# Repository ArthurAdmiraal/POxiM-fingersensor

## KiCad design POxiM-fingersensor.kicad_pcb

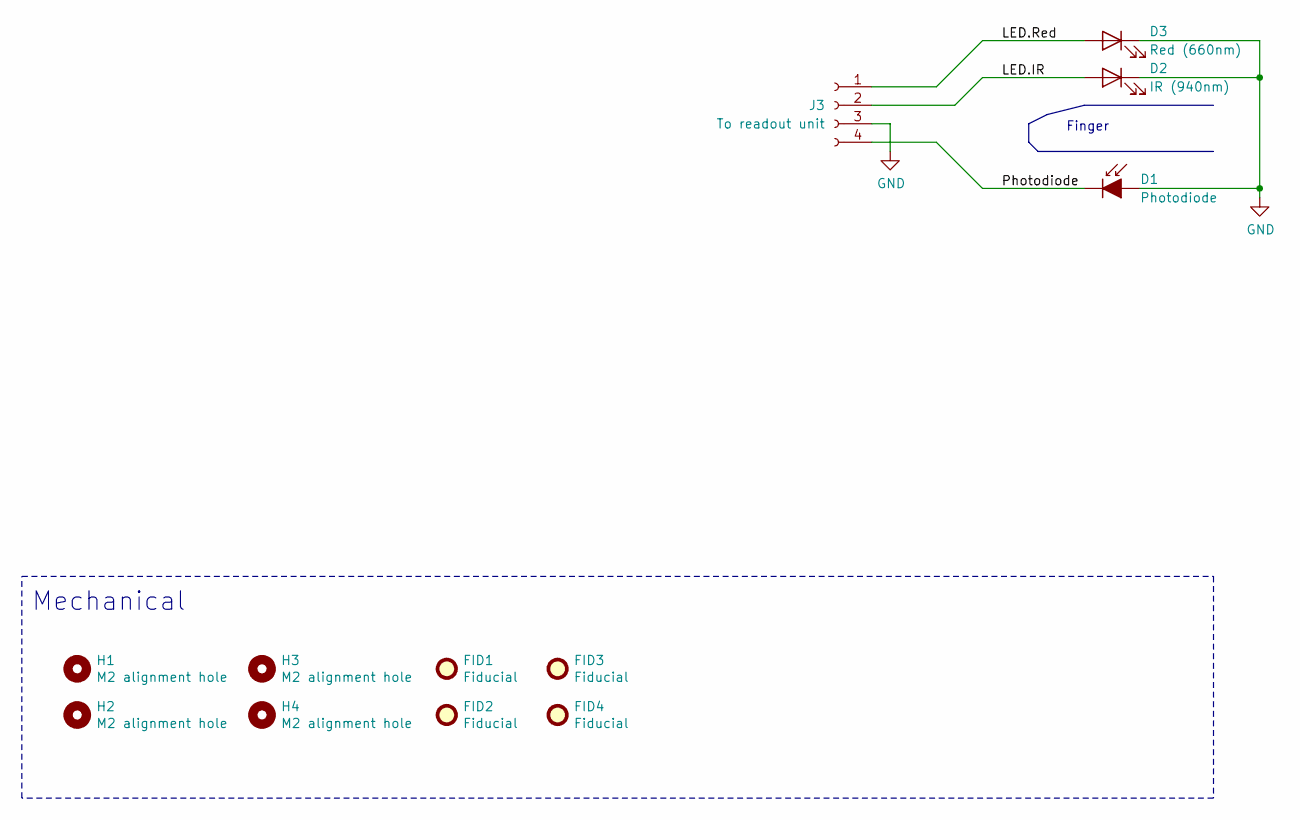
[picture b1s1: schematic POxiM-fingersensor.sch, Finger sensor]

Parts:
D1: Photodiode; LED_1206_3216Metric_0805_2012Metric_Castellated; Part number SFH 2701
D2: IR (940nm); LED_0805_2012Metric_0603_1608Metric; Part number APTD2012F3C
D3: Red (660nm); LED_0805_2012Metric_0603_1608Metric; Part number SML-LX0603SRW-TR
FID1, FID2, FID3, FID4: Fiducial; Fiducial_1mm_Mask2mm
H1, H2, H3, H4: M2 alignment hole; AlignmentHole_2mm
J3: To readout unit; Finger-CableConnection

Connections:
/LED.IR: D2.2 (A), J3.2
/LED.Red: D3.2 (A), J3.1
/Photodiode: D1.1 (K), J3.4
GND: D1.2 (A), D2.1 (K), D3.1 (K), J3.3

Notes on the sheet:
Finger
Mechanical

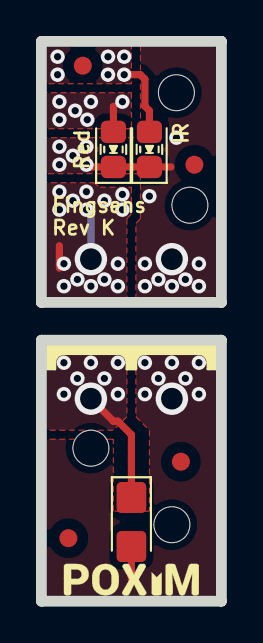
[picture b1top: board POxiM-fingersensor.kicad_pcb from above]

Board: 2 copper layers, 10.0 x 31.1 mm, 12 parts (1 on the bottom side), 4 nets.

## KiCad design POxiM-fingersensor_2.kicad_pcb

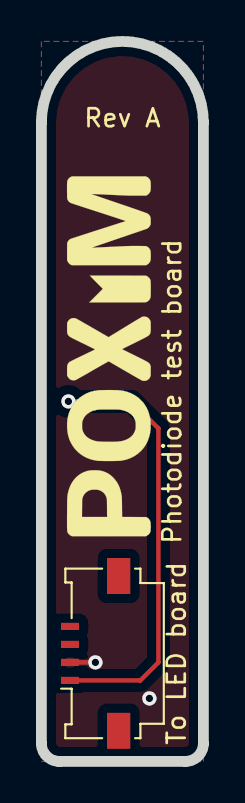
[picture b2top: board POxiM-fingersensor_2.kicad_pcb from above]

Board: 2 copper layers, 9.0 x 40.0 mm, 3 parts (1 on the bottom side), 2 nets.

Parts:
CA1: 50mm FFC; Accesory
D1: Photodiode; LED_1206_3216Metric_Castellated
J1: To LED board; Molex_200528-0040_1x04-1MP_P1.00mm_Horizontal

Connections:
GND: D1.2, J1.2
unnamed: D1.1, J1.1

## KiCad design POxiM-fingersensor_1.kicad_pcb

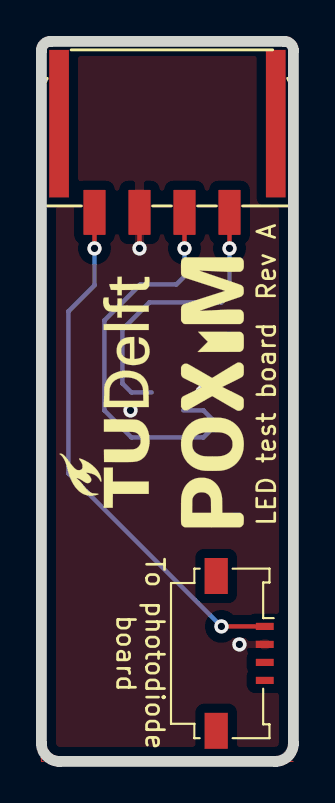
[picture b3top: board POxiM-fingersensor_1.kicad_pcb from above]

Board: 2 copper layers, 14.0 x 40.0 mm, 4 parts (1 on the bottom side), 4 nets.

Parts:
CA1: 50mm FFC; Accesory
D2: IR and red; VSMD66694
J2: To photodiode board; Molex_200528-0040_1x04-1MP_P1.00mm_Horizontal
J3: To readout unit; Molex-Nanofit-4

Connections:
GND: D2.1, D2.3, J2.2, J3.2
unnamed: D2.2, J3.4
unnamed: D2.4, J3.3
unnamed: J2.1, J3.1

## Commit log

2020-04-27 mechanical symbol library added and submodule update
2020-04-27 Draft scheematic
2020-04-27 Add purchasing information
2020-04-30 Finish Rev A
2020-04-30 Update libraries
2020-05-28 Prepare and export schematic
2020-06-10 Move to flelex layout
2020-06-17 Finger sensor rev C
2020-06-17 Create rigid option Rev D
2020-06-19 Export step, decals
2020-06-20 Rev F
2020-06-24 export steps
2020-07-01 Export rev F
2020-07-01 Rev G
2020-07-01 Remove sollder paste from finger sensor connection
2020-07-01 Increase cable connection clearance
2020-07-01 Rev H
2020-07-07 Rev I
2020-07-07 Rev J
2020-07-22 Rev K
